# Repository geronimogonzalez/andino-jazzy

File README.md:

<div align="center">

</div>

<div align="center">

</div>

[**UNSTABLE BRANCH**]

Andino is a fully open-source diff drive robot designed for educational purposes and low-cost applications.
It is fully integrated with ROS 2 and it is a great base platform to improve skills over the robotics field.
With its open-source design, anyone can modify and customize the robot to suit their specific needs.

_Note: For videos go to [Media](#selfie-media) section._

## :books: Package Summary

- :rocket: [`andino_bringup`](./andino_bringup): Contains mainly launch files in order to launch all related driver and nodes to be used in the real robot.
- :robot: [`andino_hardware`](./andino_hardware): Contains information about the Andino assembly and hardware parts.
- :ledger: [`andino_description`](./andino_description): Contains the URDF description of the robot.
- :hammer_and_pick: [`andino_firmware`](./andino_firmware): Contains the code be run in the microcontroller for interfacing low level hardware with the SBC.
- :gear: [`andino_base`](./andino_base): [ROS Control hardware interface](https://control.ros.org/master/doc/ros2_control/hardware_interface/doc/writing_new_hardware_interface.html) is implemented.
- :control_knobs: [`andino_control`](./andino_control/): It launches the [`controller_manager`](https://control.ros.org/humble/doc/ros2_control/controller_manager/doc/userdoc.html) along with the [ros2 controllers](https://control.ros.org/master/doc/ros2_controllers/doc/controllers_index.html): [diff_drive_controller](https://control.ros.org/master/doc/ros2_controllers/diff_drive_controller/doc/userdoc.html) and the [joint_state_broadcaster](https://control.ros.org/master/doc/ros2_controllers/joint_state_broadcaster/doc/userdoc.html).
- :world_map: [`andino_slam`](./andino_slam/): Provides support for SLAM with your `andino` robot.
- :compass: [`andino_navigation`](./andino_navigation/): Navigation stack based on `nav2`.

## :paperclips: Related projects

Other projects built upon Andino! :rocket:

- :computer: [`andino_gz`](https://github.com/Ekumen-OS/andino_gz): [Gazebo](https://gazebosim.org/home)(non-classic) simulation of the `andino` robot.
- :lady_beetle: [`andino_webots`](https://github.com/Ekumen-OS/andino_webots): [Webots](https://github.com/cyberbotics/webots) simulation of the Andino robot fully integrated with ROS 2.
- :joystick: [`andino_o3de`](https://github.com/Ekumen-OS/andino_o3de): [O3DE](https://o3de.org/) simulation of the Andino robot.
- :green_circle: [`andino_isaac`](https://github.com/Ekumen-OS/andino_isaac): [Isaac Sim](https://docs.omniverse.nvidia.com/isaacsim/latest/index.html) simulation of the Andino robot.
- :robot: [`andino_rmf`](https://github.com/Ekumen-OS/andino_rmf): [OpenRMF](https://www.open-rmf.org/) integration of Andino simulation.
- :test_tube: [`andino_integration_tests`](https://github.com/Ekumen-OS/andino_integration_tests): Extension to the Andino robot showing how to build integration tests.

## :busts_in_silhouette: Community

 Join our Discord and contribute to the community!

## :pick: Robot Assembly

Visit [`andino_hardware`](./andino_hardware/) for assembly instructions.

## :mechanical_arm: Installation

### Platforms

- ROS 2: Jazzy Jalisco
- OS:
  - Ubuntu 24.04 Noble Numbat
  - Ubuntu Server 24.04.1 (WIP) (On real robot (e.g: Raspberry Pi 4B))

### Build from Source

#### Dependencies

1. Install [ROS 2](https://docs.ros.org/en/jazzy/Installation/Ubuntu-Install-Debs.html)
2. Install [colcon](https://colcon.readthedocs.io/en/released/user/installation.html)

#### colcon workspace

Packages here provided are colcon packages. As such a colcon workspace is expected:

1. Create colcon workspace

```
mkdir -p ~/ws/src
```

2. Clone this repository in the `src` folder

```
cd ~/ws/src
```

```
git clone https://github.com/Ekumen-OS/andino.git
```

3. Install dependencies via `rosdep`

```
cd ~/ws
```

```
rosdep install --from-paths src --ignore-src -i -y
```

4. Build the packages

```
colcon build
```

5. Finally, source the built packages
   If using `bash`:

```
source install/setup.bash
```

`Note`: Whether your are installing the packages in your dev machine or in your robot the procedure is the same.

### Install the binaries

The packages have been also released via ROS package manager system for the 'humble' distro. You can check them [here](https://repo.ros2.org/status_page/ros_humble_default.html?q=andino).

These packages can be installed using `apt` (e.g: `sudo apt install ros-humble-andino-description`) or using `rosdep`.

## :rocket: Usage

### Robot bringup

`andino_bringup` contains launch files that concentrates the process that brings up the robot.

After installing and sourcing the andino's packages simply run.

```
ros2 launch andino_bringup andino_robot.launch.py
```

This launch files initializes the differential drive controller and brings ups the system to interface with ROS.
By default sensors like the camera and the lidar are initialized. This can be disabled via arguments and manage each initialization separately. See `ros2 launch andino_bringup andino_robot.launch.py -s ` for checking out the arguments.

- include_rplidar: `true` as default.
- include_camera: `true` as default.

After the robot is launched, use `ROS 2 CLI` for inspecting environment.
For example, by doing `ros2 topic list` the available topics can be displayed:

    /camera_info
    /cmd_vel
    /image_raw
    /odom
    /robot_description
    /scan
    /tf
    /tf_static

   _Note: Showing just some of them_

### Teleoperation

Launch files for using the keyboard or a joystick for teleoperating the robot are provided.

#### Keyboard

```
ros2 launch andino_bringup teleop_keyboard.launch.py
```
This is similarly to just executing `ros2 run teleop_twist_keyboard teleop_twist_keyboard`.

#### Joystick

Using a joystick for teleoperating is notably better.
You need the joystick configured as explained [here](andino_hardware/README.md#Using-joystick-for-teleoperation).
```
ros2 launch andino_bringup teleop_joystick.launch.py
```

### RViz

Use:

```
ros2 launch andino_bringup rviz.launch.py
```

For starting `rviz2` visualization with a provided configuration.

## :compass: Navigation

The [`andino_navigation`](./andino_navigation/README.md) package provides a navigation stack based on the great [Nav2](https://github.com/ros-planning/navigation2) package.

https://github.com/Ekumen-OS/andino/assets/53065142/29951e74-e604-4a6e-80fc-421c0c6d8fee

Follow the [`andino_navigation`'s README](./andino_navigation/README.md) instructions for bringing up the Navigation stack in the real robot or in the simulation.

## :selfie: Media

### RVIZ Visualization

https://github.com/Ekumen-OS/andino/assets/53065142/c9878894-1785-4b81-b1ce-80e07a27effd

### Slam

Using the robot for mapping.

https://github.com/Ekumen-OS/andino/assets/53065142/283f4afd-0f9a-4d37-b71f-c9d7b2f3e453

https://github.com/Ekumen-OS/andino/assets/53065142/d73f6053-b422-4334-8f62-029a38799e66

See [`andino_slam`](./andino_slam/) for more information.

## :robot: Share your Andino!

Have you built your `Andino` already? Please go to [`Show & Tell`](https://github.com/Ekumen-OS/andino/discussions/categories/show-and-tell) Discussion and share with us your own version of it.

## :star2: Inspirational sources

This section is dedicated to recognizing and expressing gratitude to the open-source repositories that have served as a source of inspiration for this project. We highly recommend exploring these repositories for further inspiration and learning.

 * [articubot_one](https://github.com/joshnewans/articubot_one)
 * [diffbot](https://github.com/ros-mobile-robots/diffbot)
 * [noah_hardware](https://github.com/GonzaCerv/noah-hardware)
 * [linorobot](https://github.com/linorobot/linorobot2)

## :raised_hands: Contributing

Issues or PRs are always welcome! Please refer to [CONTRIBUTING](CONTRIBUTING.md) doc.

## Code development

Note that a [`Docker`](./docker) folder is provided for easy setting up the workspace.

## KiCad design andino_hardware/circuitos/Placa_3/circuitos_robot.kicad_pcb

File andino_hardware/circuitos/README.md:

# Robot Andino
###### Repositorio de la rama de _Geronimo Ferraris_

## Introducción:

En esta rama tomada de la **rama main** del repositorio general agregaré las carpetas y archivos que creo necesario para la construcción del **Robot Andino**.

### Carpeta _circuitos_
Esta carpeta contiene los archivos de kicad donde estará un esquemático de los circuitos necesarios para el robot. A su vez estarán también los archivos necesarios para la creación del **PCB**. 

### Carpeta _imagenes_
Aquí estarán todas las imágenes de los distintos procesos realizados durante la creación del robot.

### Archivo _informe_
Este archivo contiene un registro de lo que se hizo cada día, además de objetivos para el próximo día.

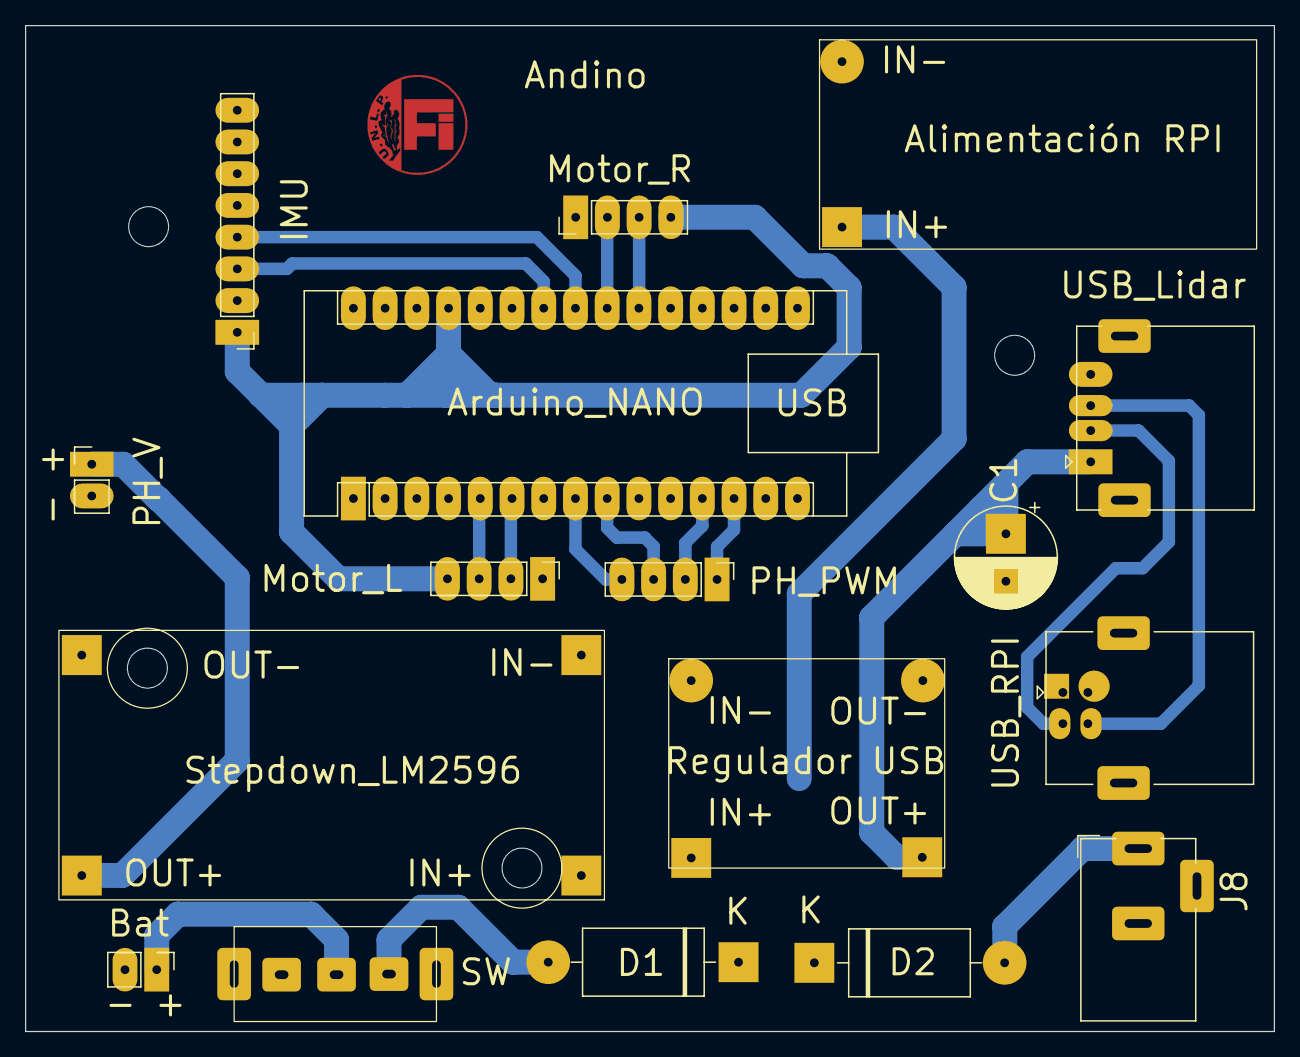
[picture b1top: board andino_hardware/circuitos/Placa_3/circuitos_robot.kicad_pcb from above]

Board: 2 copper layers, 100.0 x 80.5 mm, 17 parts (0 on the bottom side), 20 nets.

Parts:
Alimentación RPI: Regulador_RPI
Arduino_NANO: Arduino_Nano_Every; Arduino_Nano
Bat: PinHeader_1x02_P2.54mm_Vertical
C1: CP_Radial_D8.0mm_P3.80mm
D1, D2: 1N5822; D_DO-201AD_P15.24mm_Horizontal
IMU: Conn_01x08_Pin; PinHeader_1x08_P2.54mm_Vertical
J8: Jack-DC; BarrelJack_CUI_PJ-102AH_Horizontal
Motor_L: Conn_01x04_Pin; PinHeader_1x04_P2.54mm_Vertical
Motor_R: Conn_01x04_Pin; PinHeader_1x04_P2.54mm_Vertical
PH_PWM: Conn_01x04_Pin; PinHeader_1x04_P2.54mm_Vertical
PH_V: PinHeader_1x02_P2.54mm_Vertical
Regulador USB: Regulador_USB
SW: SW_17,2*7,6; SW_17,2_7,6
Stepdown_LM2596: Stepdown_LM2596
USB_Lidar: USB_A; USB_A_CONNFLY_DS1095-WNR0
USB_RPI: USB_B; USB_B_Lumberg_2411_02_Horizontal

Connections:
5V: C1.1, Regulador USB.4, USB_Lidar.1 (VBUS)
5V_Ard: Arduino_NANO.27 (+5V), IMU.1, Motor_L.4, Motor_R.4
9V: PH_V.1, Stepdown_LM2596.3
12V: Alimentación RPI.2, D1.1 (K), D2.1 (K), Regulador USB.2, Stepdown_LM2596.1
12V_Bateria: Bat.1, SW.2
12V_Fuente: D2.2 (A), J8.1
D+: USB_Lidar.3 (D+), USB_RPI.3 (D+)
D-: USB_Lidar.2 (D-), USB_RPI.2 (D-)
Encoder_L_pinA: Arduino_NANO.21 (A2), Motor_R.3
Encoder_L_pinB: Arduino_NANO.22 (A3), Motor_R.2
Encoder_R_pinA: Arduino_NANO.5 (D2), Motor_L.3
Encoder_R_pinB: Arduino_NANO.6 (D3), Motor_L.2
GND: Alimentación RPI.1, Arduino_NANO.4 (GND), Arduino_NANO.29 (GND), Bat.2, C1.2, IMU.2, J8.2, Motor_L.1, Motor_R.1, PH_V.2, Regulador USB.1, Regulador USB.3, SW.4, Stepdown_LM2596.2, Stepdown_LM2596.4, USB_Lidar.4 (GND), USB_Lidar.5 (Shield), USB_RPI.4 (GND), USB_RPI.5 (Shield)
unnamed: D1.2 (A), SW.3
PWM1: Arduino_NANO.8 (D5), PH_PWM.4
PWM2: Arduino_NANO.12 (D9), PH_PWM.2
PWM3: Arduino_NANO.9 (D6), PH_PWM.3
PWM4: Arduino_NANO.13 (D10), PH_PWM.1
SCL: Arduino_NANO.24 (SCL/A5), IMU.3
SDA: Arduino_NANO.23 (SDA/A4), IMU.4

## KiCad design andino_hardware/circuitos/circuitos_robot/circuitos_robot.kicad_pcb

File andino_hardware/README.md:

# andino_hardware

This package aims to provide the necessary information to the correct assembly of the robot.

## Bill of Materials

| Number | Module | Part | Links | Comments |
|:--:|:--:|:-----------------------:|:--------------------:|:-------------------------------------------------------:|
| 1 | SBC | Raspberry Pi 4 B (4 Gb) | [PiShop](https://www.pishop.us/product/raspberry-pi-4-model-b-2gb/), [TiendaTec](https://www.tiendatec.es/raspberry-pi/gama-raspberry-pi/1100-raspberry-pi-4-modelo-b-4gb-5056561800349.html) | If you want better performance you could buy the 8GB model |
| 2 | Chassis |  2 x Print 3d Chassis + Rubber Tyre Wheels | [Chassis](./printing_model/chassis/), [Wheels Sparkfun](https://www.sparkfun.com/products/13259) | - |
| 3 | Motors | 2 x Motor with Encoder | [Sparkfun](https://www.sparkfun.com/products/16413) | - |
| 4 | Microcontroller | Arduino Nano | [Amazon](https://www.amazon.es/RUIZHI-Interfaz-Controlador-Mejorada-Compatible/dp/B0CNGKG4MZ/ref=sr_1_6?dib=eyJ2IjoiMSJ9.gnHfW9VtlEjMns12dAyHXLyFAlaikWpFyoOQJpO0iJBR-zelggQTQ9n001SH_P6NQ9DO3gPetP2krm7GAGvJus6vz4Utqu8Hy1gol0Rq7nmtJITd70ZNi3linf9v1g1iP7MlBx98cBGLVvFy-O2kZnJ63uZDwOZzwz_kExJzUWAxroO3AjufqqGOQHswLfDfjH6jpOJt54xxpCaqurDccId2O0uGKOj6WpPz6iLSubpsPB479SWYPSncxWQzz2kO4VjT6HVzPS2uWi19TS-A9WXVZceLBiz9t25Pf39jiGQ.1sLxrQ94HdIoXBq4VcDFMZhzKoL3wyJoY-U6BmDI6fY&dib_tag=se&keywords=arduino+nano+v3&qid=1714468231&sr=8-6) | You can also use an Arduino Uno, but mind size. It should include a microUSB - USB cable. If not, you will need to purchase it.  |
| 5 | Motor Driver | L298N Dual H Bridge | [Amazon](https://www.amazon.com/Bridge-Stepper-Driver-Module-Controller/dp/B09T6K9RFZ/ref=sr_1_4?crid=37YY7JO6C3WVE&keywords=l298&qid=1685740618&sprefix=l29%2Caps%2C277&sr=8-4) | - |
| 6 | Laser Scanner | RPLidar A1M8 | [RobotShop](https://www.robotshop.com/products/rplidar-a1m8-360-degree-laser-scanner-development-kit?_pos=3&_sid=b0aefcea1&_ss=r), [Amazon](https://www.amazon.es/dp/B07VLFGT27?ref_=cm_sw_r_cso_wa_apan_dp_RJ3AZC2XCEVDK0X2DCGA&starsLeft=1&th=1) | If no microUSB-USB cable is included, you will need to purchase one |
| 7 | Camera | Raspi Camera Module V2, 8 MP | [Robotshop](https://www.robotshop.com/products/raspberry-pi-camera-module-v2), [Amazon](https://www.amazon.com/Raspberry-Pi-Camera-Module-Megapixel/dp/B01ER2SKFS?th=1), [Longer cable](https://www.amazon.es/AZDelivery-Repuesto-Raspberry-30cm-Flexkabel/dp/B01NAXKTDP/ref=sr_1_9?__mk_es_ES=%C3%85M%C3%85%C5%BD%C3%95%C3%91&crid=I1IK0FQVQCCU&dib=eyJ2IjoiMSJ9.2UYb-3a8M00iHZZiHT0xjp8vfzq-3BSmJSLxdtcCMV6WMj8g5T8T_j5DKX8cESxqnVN01YpV3nX28IuhewGTOsmJ4yF5st20TxU7kHNHftZE_aygB5vT-001wEvUfx70V0H0DZljw0YfC4R2wpjsTR_89pAA95C4F8LhJiGbbUGTEjBgmjnsRIFs6FYatZa9KVusNyv2cKxGZlav36gdoAkMXQUvX578c6frxSnH5DROCeK6bKSqrczA7R8OBVWC995fK1AxHbJLHZJEDQGXMVhUkHd2liBV0nq48mnyE6Q.nHty4TxSpldkH8FZAia_rx7sX6c2uIBpPRUEqwq5NiY&dib_tag=se&keywords=raspberry%2Bpi%2Bcamera%2Bcable&qid=1716878948&sprefix=raspberry%2Bpi%2Bcamera%2Bcable%2Caps%2C76&sr=8-9&th=1)  | A link for a longer cable (30 cm) is included, just in case the one included with the camera is too short. |
| 8 | Electrical Power Supply | Powerbank 5V | [Amazon](https://www.amazon.es/Heganus-Powerbank-10000mAh-port%C3%A1til-pr%C3%A1ctico/dp/B082PPPWXY/ref=asc_df_B082PPPWXY/?tag=googshopes-21&linkCode=df0&hvadid=420334509253&hvpos=&hvnetw=g&hvrand=13392500367381615369&hvpone=&hvptwo=&hvqmt=&hvdev=c&hvdvcmdl=&hvlocint=&hvlocphy=9181150&hvtargid=pla-878722533582&psc=1&mcid=642b7553488f350a8726c7bfb183a667&tag=&ref=&adgrpid=95757266066&hvpone=&hvptwo=&hvadid=420334509253&hvpos=&hvnetw=g&hvrand=13392500367381615369&hvqmt=&hvdev=c&hvdvcmdl=&hvlocint=&hvlocphy=9181150&hvtargid=pla-878722533582) | Any powerbank is suitable: Mind size / weight / output current(>=2A) |
| 9 | Power Step up | DC - DC boost converter | [Amazon Europe](https://www.amazon.es/Convertidor-convertidor-Controlador-almacenamiento-Transformadores/dp/B08D5XF571) | If motors support higher voltage than 5V a step-up(e.g: to 9V) can be added between powerbank (5V) and motor driver. Screw clockwise to reduce the output voltage. |
| 10 | Fixing & Mount | M3 bolts/fasteners - M3 Spacers - M2.5/2.0 bolts/fasteners for SBC | [Mercado Libre](https://articulo.mercadolibre.com.ar/MLA-823234605-kit-tornillos-electronica-500-unid-fresada-philips-m3-oferta-_JM#position=1&search_layout=stack&type=item&tracking_id=2a14497e-a3dc-4a0f-98fb-b3b524117284), [Amazon](https://www.amazon.com/Taiss-620PCS-Metric-Assortment-Washers/dp/B0CWXRG6VL/ref=sr_1_2_sspa?crid=3R3BT7LOQWZ4B&dib=eyJ2IjoiMSJ9.EBY3VtTnCGRri20ECsEwpF2eTrWOhlADXq8Rbv78LP7JVW0giUfPQ5-G3e5cVq7svNoKIPbFGf0jQoImIPuJvU72yWC0XaaXyHE03TjX1zVT-AxcCUr6bvvqnQrrwFNowZjHy2ZibnHX4sDMx3aixEmx5XUGq43KVEID5FIGzTw6xsLQd410DewktxUFWCHLSD8HR8BeAUKcP3mzciuPmc8dcz9TzY5cZ_wYFO-WyEQ.B5-OkrGZbzkIn8cw4Zb_LtQUoxX1qKuiVqI6PTNmpZk&dib_tag=se&keywords=kit+M3+tuercas+y+tornillos&qid=1714469030&sprefix=kit+m3+tuercas+y+tornillos%2Caps%2C149&sr=8-2-spons&sp_csd=d2lkZ2V0TmFtZT1zcF9hdGY&psc=1), [Spacers](https://www.amazon.es/YOKIVE-Separadores-Tornillos-Hexagonal-Consistente/dp/B0BWXL75R6/ref=sr_1_11?__mk_es_ES=%C3%85M%C3%85%C5%BD%C3%95%C3%91&crid=39R5HOTYH2AC9&dib=eyJ2IjoiMSJ9.7A-mx6__B2agU-KSbpRPhlNj2WkQfkj8OtZKEmwlwHa3NiDqUA-1Um0339r3Ssad0h03L471s08VcgBGByJpKwummUR8Sgyt3AuF4sahKIacNlyBlD8mcl3bNQ54HR8L585aepoUOxllFXUi2AEGde8kjkNqaiOEcyflppOf1eKtAtlyTYnnjOVJs5YqRK97QV3pUt1g8Rt1zLn7RsEtRrvlMQIXXBjIFFZsqK2tN7OBY2lgorgdRsXP1aS5tad9rD9vsl9SkPUx_c1Bf0ulzabNSFk19v_cSd0IwEx2zSw.30hsx31Q_-5A3eLrlOwhoTvAs_yDufCk04NiN0xk0C8&dib_tag=se&keywords=spacer+30mm+m3&qid=1716156793&refinements=p_n_free_shipping_eligible%3A20930980031&rnid=20930979031&sprefix=spacer+30mm+m3%2Caps%2C107&sr=8-11) | You will probably need to replace the default spacers for the LiDAR with M3 spacers |
| 11 | Other 3D printed parts | Camera Mount | [3D models](./printing_model/raspi_cam_mount/) | These parts are for fixing the Raspi Cam at the front of the robot |
| 12 | Caster wheel | Caster wheel | [Amazon](https://www.amazon.es/Unidades-Peque%C3%B1as-Dispositivo-Transferencia-Transporte/dp/B098XHYW7F/ref=asc_df_B098XHYW7F/?tag=googshopes-21&linkCode=df0&hvadid=529604577974&hvpos=&hvnetw=g&hvrand=15132275207682237467&hvpone=&hvptwo=&hvqmt=&hvdev=c&hvdvcmdl=&hvlocint=&hvlocphy=9181150&hvtargid=pla-1396749454795&psc=1&mcid=b1df85a65d163e89b507de60e73f9e65) | - |
| 13 | SD Card | 64 GB SD Card | [Apokin](https://www.apokin.es/tarjeta-microsd-philips-64gb-class10.html), [Amazon](https://www.amazon.es/Kingston-Tarjeta-SDCS2-64GB-Adaptador/dp/B07YGZQ4H8/ref=sr_1_7?dib=eyJ2IjoiMSJ9.zE4PI6DCNK3d78rtl5ga1NQXGwJT1jC2iqi3mXNzbdJ4BosAUPCn9gc13Gc7pdHDx-7wTy4CDj0zIlgDpu9qXH-6GLgI--pJbfi3OvTBPhwwH-tfi1OzM9xqcAOJG6pJuTtkknsyFk6Ma2EHJ4UdheaziDC_KKaWNKgsf_DFbcA-ZxQSXlTtQqwHvCzgi8hq4vKGiEIY-LSZS_sXE9IUGroo0Isl59Po2IXhTBG5IHnnsVR_7lo0dVBVFYl-5GY2CvJbrixULuPl90TbFTTP6DoIeDcpFdDTcbvSK3Lecss.WXBgIZllFgQxx13Szl3q6WIlTOliwrN8V42J1SzNJ8o&dib_tag=se&qid=1714552555&refinements=p_n_feature_browse-bin%3A948155031&s=computers&sr=1-7) | The SD Card is used to host the OS for the Raspberry Pi |
| 14 | (Optional) Plastic seals | - | - | You will need at least 2 longer ones to fix the powerbank to the upper chassis, and the shorter ones for all the wires. If you don't want to use them, you can use other method to fix the powerbank and wires |

When you gather all the parts, you should have the following (NOTE: the printed encoder wheels are no longer necessary, since the motors are equipped with an embedded encoder):

### Tooling

| Number | Tool | Links | Comments |
|:--:|:------:|:--------------------:|:-------------------------------------------------------:|
| 1 | Set of screwdrivers | [Amazon](https://www.amazon.es/Ainiv-Destornilladores-Precisi%C3%B3n-Destornillador-magnetizador/dp/B09CD1F44B/ref=asc_df_B09CD1XT57/?tag=googshopes-21&linkCode=df0&hvadid=529495276761&hvpos=&hvnetw=g&hvrand=2854754490438163902&hvpone=&hvptwo=&hvqmt=&hvdev=c&hvdvcmdl=&hvlocint=&hvlocphy=9181160&hvtargid=pla-1431590275356&mcid=4f49c0c6c8ca33b390169090ae4ad15b&th=1) | You need flat and star screwdrivers |
| 2 | Silicon Pistol | [Amazon](https://www.amazon.es/Tilswall-Pegamento-Manualidades-Bricolaje-Reparaciones/dp/B07TD1RD4R/ref=pd_ci_mcx_pspc_dp_d_2_i_1?pd_rd_w=49k0d&content-id=amzn1.sym.f11fe75a-7397-412e-9b90-7e09bf6f5c14&pf_rd_p=f11fe75a-7397-412e-9b90-7e09bf6f5c14&pf_rd_r=MA73TQJTYS2GMC7XW7YC&pd_rd_wg=Z3aRz&pd_rd_r=08e805c6-81b7-4023-8ea1-9b357536cba1&pd_rd_i=B07TD1RD4R&th=1) | This pistol should include 75 silicon bars so you won't need to purchase them separately |

## Assembly Process

  1. Screw the Motor Driver and the idler wheel to the lower chassis.

  Here you have a front image of how the caster wheel are mounted to the chassis:

  2. Screw the 3D printed parts for the Raspi Camera Module:

  3. Add the Arduino Nano to the back of the lower part of the chassis. It should look like this:

  4. Screw the Raspberry Pi and the DC-DC converter to the front of the lower part of the chassis:

  5. Fix the powerbank to the back of the upper part of the chassis:

  6. Add the RPLidar to the front of the upper part of the chassis:

  7. Add the IMU (WIP)

  <!-- TODO Add photo of the IMU physical implementation-->

  8. Perform all the wiring following the [Connections Diagram](#connection-diagram) of both the upper and lower chassis. Note that some of the connections may need to be done by soldering the cables.

  9.  Join both chassis together, and complete the remaining wiring to have your robot ready:

## Connection Diagram

### Motor-Arduino

Some frequent errors:
 - If one of the motors rotates in the opposite direction (think about the orientation of the motors in the chassis) probably the output(+ and -) of the L298N's output should be toggled.
 - When moving forward the encoder values should increase while moving backwards they should decrease. If it is happening the other way around probably the A and B encoder signals should be toggled.

### Raspberry-Power

*NOTE: depending on the power bank maximum output current, the motors may need to be powered with a voltage value lower than 9V. While a higher voltage value (up to 9V) leads to smoother operation (better motor speed control), it also increases their open-loop speed, which is noticeable particularly during motion start and varies according to the power bank quality (output current capabilities). Therefore, adjusting the output voltage to lower values (around 7V) may be required so as to make the motors work as expected.

**NOTE: Ensure the ribbon cable is properly connected with the blue or silver side facing the USB ports.

## Microcontroller Configuration

For uploading the microcontroller firmware please refer to [`andino_firmware`](../andino_firmware/README.md) package.

## Single Board Computer (SBC)

The SBC used in this project is a Raspberry Pi 4b so the guidelines here will refer particularly to this family of on-board computers, however extending its use to other families is possible as well.

### Operative System [WIP]

Ubuntu Server 24.04.1 is the recommended operative system for this project if you want to use the `jazzy` distro, since Ubuntu Mate 24 is not yet released.

For installing this OS in the Raspberry:
1. Download the image from here: [download Ubuntu 24 for Raspberry](https://ubuntu.com/download/raspberry-pi)

2. Install OS to a microSD card using [Raspberry Pi Imager](https://www.raspberrypi.com/software/).
   - No extra configuration should be necessary.

3. Boot your raspberry using the microSD and a HDMI connection. Some initial configuration is necessary. Follow the wizard for a proper set up. It is recommended to use simple User and Password combinations for the user. For example:
    - user: pi
    - password: admin
      
**recordar que el primer arranque debe ser conectado a internet mediante cable ethernet**

4. Once is done, run `sudo apt update && sudo apt upgrade` in a terminal for updating the system. Then reboot.

Para configurar la conecxion wifi descargar el paquete network manager
```
sudo apt-get install network-manager
```
y utilizar el comando 
```
sudo nmtui
```
para la configuracion de la red wifi deseada.

Recomendacion: Siempre trabajar con la mayor velocidad posible, por lo que si es posible trabajar bajo wifi 5.0 o cableado al menos una de las computadoras (ROV o station).
### Installing dependencies

Some packages are necessary to be installed towards a correct set up of the robot's on-board computer.

#### ssh-server

In general, you will want to access to the Raspberry remotely via `ssh` connection while being connected in the same network.
So we need to install `ssh-server`;
```
sudo apt-get install openssh-server
```
Enable it if it is not enabled yet:
```
sudo systemctl enable ssh --now
```

After this you will be able to access this device from a remote computer by doing:
```
ssh <user>@<ip>
```
For example if the user is `pi` and the ip is `192.168.0.102`
```
ssh pi@192.168.0.102
```

#### Common utilities

Install some common utilities that will be required later on.

```
sudo apt update
```

```
sudo apt install git net-tools software-properties-common build-essential -y
```
<font color="red"> el comando de abajo no existe. No lo corro y veo</font>

```
sudo apt install python3-rosdep2 python3-catkin-pkg python3-catkin-pkg-modules python3-rospkg-modules python3-rospkg  -y
```

#### Install ROS

Follow suit the instructions for installing next dependencies from binaries:
 - [ROS 2 Jazzy](https://docs.ros.org/en/jazzy/Installation/Ubuntu-Install-Debs.html)

Nota: Instalar ROS Jazzy Desktop, ya que contiene instaladas herramientas necesarias.

To automatically source ROS installation, it is recommended to add `source /opt/ros/humble/setup.bash` line to the `~/.bashrc` file.

#### Arduino

Arduino drivers are necessary for the SBC (Raspberry) <--> Microcontroller(Arduino) serial communication.

```
sudo apt install arduino
```

Configure it properly:
1. Add user to `dialout` and `plugdev` groups:
   ```
   sudo usermod -a -G dialout $USER
   ```
   ```
   sudo usermod -a -G plugdev $USER
   ```
   Note you will need a reboot after this to be effective.

#### Raspberry Camera Module V2

After connecting the camera module to the Raspberry's camera port.
```
sudo apt install libraspberrypi-bin v4l-utils
```
```
sudo usermod -aG video $USER
```

Check camera status:
```
vcgencmd get_camera
```

If the output of the previous command is `supported=1 detected=1', everything is fine. If not, your camera won't work correctly, you need to perform some configuration first.

Modify the `config.txt` file for the boot:

```sh
 sudo nano /boot/firmware/config.txt
```

And add these lines:

```
# Autoload overlays for any recognized cameras or displays that are attached
# to the CSI/DSI ports. Please note this is for libcamera support, *not* for
# the legacy camera stack
start_x=1
gpu_mem=128
```

Save and close the file. Then we need to enable the camera support for the raspberry:

```sh
sudo raspi-config
```

Go to `Interface Options`, select `camera` and enable it.

Finally, you just need to reboot and the camera should be working fine.

#### RPLidar installation

The installation of the A1M8 RPLidar sensor is quite straight forward and a ros integration package will be installed later on via `rosdep`.

For now, after connecting it to the usb port:
 1. Verify USB connection: Green light in the usb conversor(A1M8 side board) should be turned on.
 2. Check the authority of RPLidar's serial-port:
    - `ls -l /dev |grep ttyUSB`
    - Add extra bits by doing `sudo chmod 666 /dev/ttyUSB<number_of_device>`

### USB Port name configuration

#### Fixed USB port names

As having multiple USB devices connected to the USB ports of the Raspberry Pi, the automatically assigned USB port numbers could unexpectedly change after a reboot.
To avoid assigning your device to a `tty_USBX` number that isn't the correct one we should assign fixed USB port name for each connected device.

The idea is to be able to generate a link between the real `ttyUSBX` port and an invented one. For this we will need to create rules, that every time the Raspberry Pi boots are executed, and therefore we
always point to the correct port name.

In order to create fixed names for the USB devices follow the instructions:

1. Check the devices you have connected:
    ```
    sudo dmesg | grep ttyUSB
    ```

    ```
    [  10.016170] usb 1-1.2: ch341-uart converter now attached to ttyUSB0
    [ 309.186487] usb 1-1.1: cp210x converter now attached to ttyUSB1
    ```
    In the setup where this was tested we have:
      -> Arduino Microcontroller -> _usb 1-1.2: ch341-uart converter now attached to ttyUSB0_
      -> A1M8 Lidar Scanner -> _usb 1-1.1: cp210x converter now attached to ttyUSB1_

    _Note: If you don't know how to identify each one you can simply connect them one by one and check this output._

2. Look for attributes for each device that we will use to anchor a particular device with a name.
  We will use the `idProduct` and `idVendor` of each device.
   - Arduino Microcontroller:
      ```
      udevadm info --name=/dev/ttyUSB0 --attribute-walk
      ```
      You should look for the `idProduct` and `idVendor` under the category that matches the usb number(1-1.X):
      In this case the `ttyUSB0` was referenced to the `usb 1-1.2`, so go to that section and find the ids:
      ```
        ATTRS{idProduct}=="7523"
        ATTRS{idVendor}=="1a86"
      ```
   - Lidar Scanner
      ```
      udevadm info --name=/dev/ttyUSB1 --attribute-walk
      ```
      In this case the `ttyUSB0` was referenced to the `usb 1-1.1`, so go to that section and find the ids:
      ```
        ATTRS{idProduct}=="ea60"
        ATTRS{idVendor}=="10c4"
      ```

3. Create the rules:

    Open the file:
    ```
    sudo nano /etc/udev/rules.d/10-usb-serial.rules
    ```

    Add the following:

    ```
    SUBSYSTEM=="tty", ATTRS{idProduct}=="7523", ATTRS{idVendor}=="1a86", SYMLINK+="ttyUSB_ARDUINO"
    SUBSYSTEM=="tty", ATTRS{idProduct}=="ea60", ATTRS{idVendor}=="10c4", SYMLINK+="ttyUSB_LIDAR"
    ```
    Note that in the `symlink` field a fixed name is indicated.

4. Re-trigger the device manager:
    ```
    sudo udevadm trigger
    ```

5. Verify
    ```
    ls -l /dev/ttyUSB*
    ```
    ```
    crw-rw---- 1 root dialout 188, 0 Sep  2 15:09 /dev/ttyUSB0
    crw-rw---- 1 root dialout 188, 1 Sep  2 15:09 /dev/ttyUSB1
    lrwxrwxrwx 1 root root         7 Sep  2 15:09 /dev/ttyUSB_ARDUINO -> ttyUSB0
    lrwxrwxrwx 1 root root         7 Sep  2 15:09 /dev/ttyUSB_LIDAR -> ttyUSB1
    ```

Done! You can always use your devices by the fixed names without using the port number.
Here, `ttyUSB_ARDUINO` and `ttyUSB_LIDAR` are fixed names for the Arduino Microcontroller and the Lidar Scanner respectively.

For more information you can take a look at this external tutorial: [Here](https://www.freva.com/assign-fixed-usb-port-names-to-your-raspberry-pi/)

### Create robot workspace

Let's create our workspace and build from source this repository.

```
cd ~
```
```
mkdir robot_ws/src -p
```
Clone this repository in the `src` folder
```
cd robot_ws/src
```
```
git clone <repository_address>
```
Install dependencies via rosdep:
```
cd ~/robot_ws
```
When it is the first time you run `rosdep`:
```
rosdep update
```
Make sure to export the `ROS_DISTRO` environment variable:
```
export ROS_DISTRO=jazzy
```
And then proceed to install the workspace dependencies:
```
sudo apt update
rosdep update
rosdep install --from-paths src --ignore-src -y
```
```
source /opt/ros/jazzy/setup.bash
```
para hacer el source permanente
```
echo "source /opt/ros/jazzy/setup.bash" >> ~/.bashrc
source ~/.bashrc
```
Note that option `-r` has been added. For ARM based processors, there are missing packages, e.g. those related to simulation. We would not try to run the simulation in the compute platform of andino, however for convenience it is added here.

Let' source the ROS Humble installation:
```
source /opt/ros/humble/setup.bash
```
Let's build the packages:
```
colcon build
```
After building is completed:
```
source install/setup.bash
```

After this, you are good to go and use the robot!
Refer to [`usage`](../README.md#usage) section.

### Extra Recommendations & Tools

#### Network
Via terminal the wifi connection can be switched by doing:

List available wifi networks:
```
sudo nmcli dev wifi list
```
Connect to the desired one:
```
sudo nmcli --ask dev wifi connect <SSID>
```

#### Copy files remotely

Using `scp` is a useful tool when copying files remotely over `ssh`.

For copying a folder from host to remote unit:
```
scp -r <path/to/folder> <remote_user>@<remote_ip>:<remote_path_to_folder>
```

#### ROS Domain ID

The domain ID is used by DDS to compute the UDP ports that will be used for discovery and communication.

When using a "public" network using the domain id is a good technique to avoid extra noise with other ROS 2 system in the same network.

See [ROS_DOMAIN_ID](https://docs.ros.org/en/humble/Concepts/Intermediate/About-Domain-ID.html)

TLDR? Export an environment variable with the same ID in **all** ROS 2 clients in the network for a correct discovery.
```
export ROS_DOMAIN_ID=<a_number_between_0_and_101>
```

#### Using joystick for teleoperation

[`andino_bringup`](../andino_bringup/launch/teleop_joystick.launch.py) package provides a launch file for launching the corresponding `ROS 2` nodes for teleoperating the robot using a joystick.

It is worth mentioning that a set up might be needed depending on the gamepad you are using. Here some general guidelines:
 - In case you are using a _Xbox One Controller_ and you want use it wireless (via USB Wirless Dongle) installing [Xone](https://github.com/medusalix/xone) is recommended.
 - Verify that your joystick is actually working on Ubuntu:
    - Some tools that might be useful:
      - `sudo apt install joystick jstest-gtk evtest`
    - Run `evtest` to check if your pad is connected:
      ```
      $ evtest
        No device specified, trying to scan all of /dev/input/event*
        Not running as root, no devices may be available.
        Available devices:
          /dev/input/event22:	Microsoft X-Box One pad

      ```
    - Alternatively, you can use `jstest-gtk` to check the controller, you will find a pretty GUI to play with.

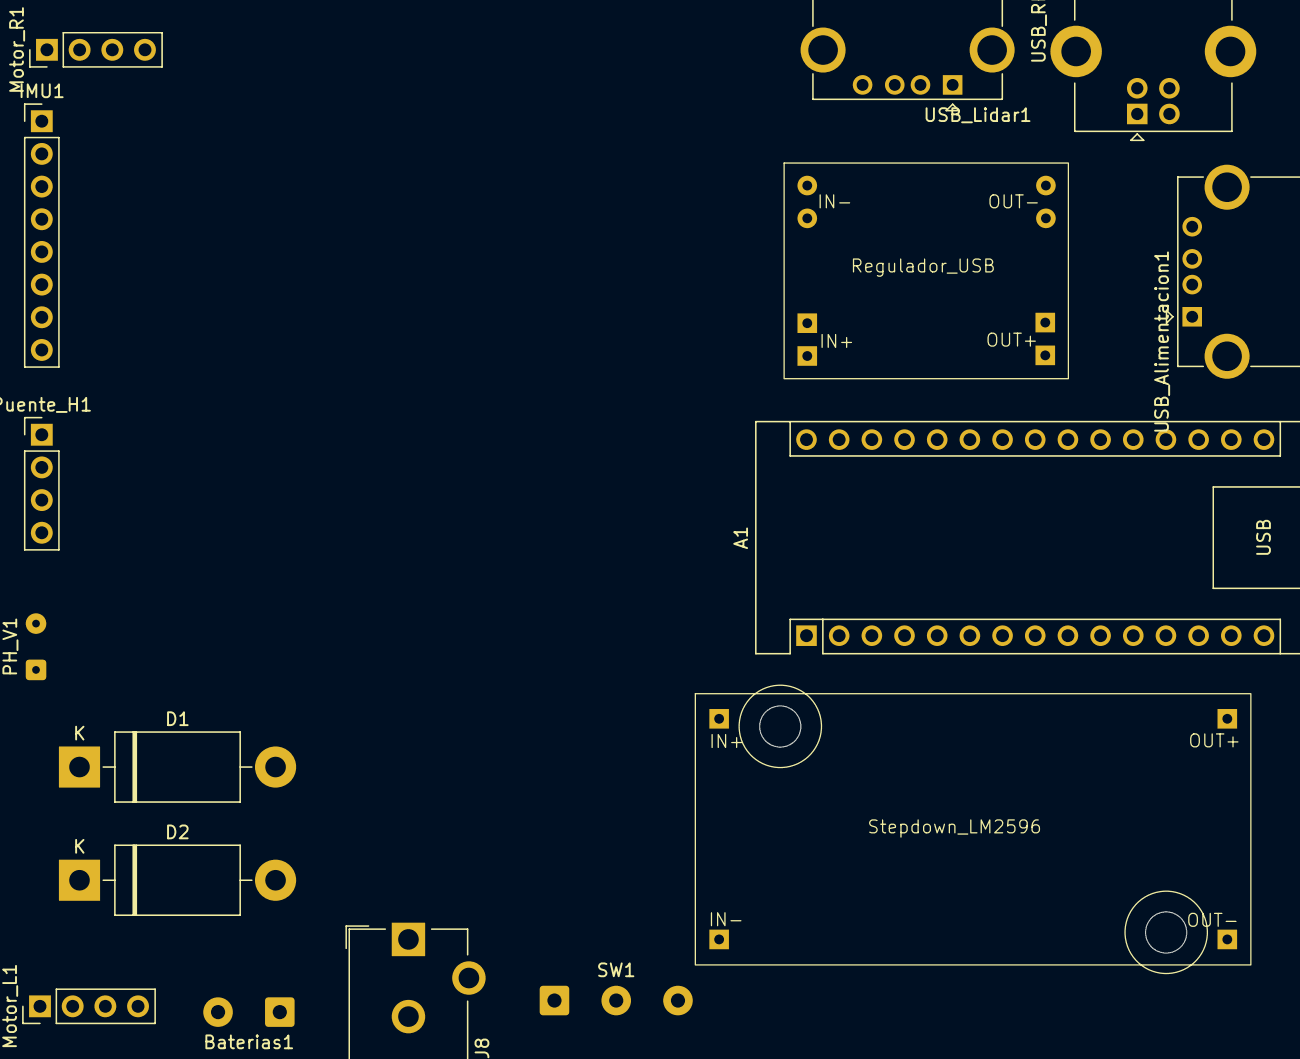
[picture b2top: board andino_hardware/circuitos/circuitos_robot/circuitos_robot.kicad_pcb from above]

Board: 2 copper layers, 16 parts (0 on the bottom side), 22 nets, no tracks yet.

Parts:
A1: Arduino_Nano_Every; Arduino_Nano
Baterias1: Conn_01x02_Pin; SolderWire-0.5sqmm_1x02_P4.8mm_D0.9mm_OD2.3mm
D1, D2: 1N5822; D_DO-201AD_P15.24mm_Horizontal
IMU1: Conn_01x08_Pin; PinHeader_1x08_P2.54mm_Vertical
J8: Jack-DC; BarrelJack_CUI_PJ-102AH_Horizontal
Motor_L1: Conn_01x04_Pin; PinHeader_1x04_P2.54mm_Vertical
Motor_R1: Conn_01x04_Pin; PinHeader_1x04_P2.54mm_Vertical
PH_V1: Conn_01x02_Pin; SolderWire-0.1sqmm_1x02_P3.6mm_D0.4mm_OD1mm
Puente_H1: Conn_01x04_Pin; PinHeader_1x04_P2.54mm_Vertical
Regulador_USB: Regulador_USB
SW1: Conn_01x03_Pin; SolderWire-0.5sqmm_1x03_P4.8mm_D0.9mm_OD2.3mm
Stepdown_LM2596: Stepdown_LM2596
USB_Alimentacion1: USB_A; USB_A_CONNFLY_DS1095-WNR0
USB_Lidar1: USB_A; USB_A_CONNFLY_DS1095-WNR0
USB_RPI1: USB_B; USB_B_Lumberg_2411_02_Horizontal

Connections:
5V: Regulador_USB.7, USB_Alimentacion1.1 (VBUS), USB_Lidar1.1 (VBUS)
5V_Ard: A1.27 (+5V), IMU1.1, Motor_L1.4, Motor_R1.4
9V: A1.30 (VIN), PH_V1.2, Stepdown_LM2596.3
12V: D1.1 (K), D2.1 (K), Regulador_USB.3, Stepdown_LM2596.1
12V_Bateria: Baterias1.1, SW1.2
12V_Fuente: D2.2 (A), J8.2
Encoder_L_pinA: A1.21 (A2), Motor_L1.3
Encoder_L_pinB: A1.22 (A3), Motor_L1.2
Encoder_R_pinA: A1.5 (D2), Motor_R1.3
Encoder_R_pinB: A1.6 (D3), Motor_R1.2
Flash: IMU1.7, Regulador_USB.2
GND: Baterias1.2, IMU1.2, J8.1, Motor_L1.1, Motor_R1.1, PH_V1.1, Regulador_USB.6, Stepdown_LM2596.2, Stepdown_LM2596.4, USB_Alimentacion1.4 (GND), USB_Lidar1.4 (GND), USB_RPI1.4 (GND)
unnamed: A1.4 (GND), A1.29 (GND)
unnamed: D1.2 (A), SW1.3
unnamed: USB_Lidar1.3 (D+), USB_RPI1.3 (D+)
unnamed: USB_Lidar1.2 (D-), USB_RPI1.2 (D-)
PWM1: A1.8 (D5), Puente_H1.4
PWM2: A1.12 (D9), Puente_H1.3
PWM3: A1.9 (D6), Puente_H1.2
PWM4: A1.13 (D10), Puente_H1.1
SCL: A1.24 (SCL/A5), IMU1.3
SDA: A1.23 (SDA/A4), IMU1.4

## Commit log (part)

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2025-10-09 Primer commit
2025-10-22 estoy probando
2025-10-22 creacion de carpetas necesarias
2025-10-23 agregue carpeta para las imagenes del proceso de construccion
2025-10-24 añadi primer README
2025-10-25 Clean up README formatting and content
    Removed unnecessary HTML tags and logos from README.
2025-10-25 Update connection details in README.md
    Updated README to reference 'hw.h' for connection details.
2025-10-30 Progreso_30/10/25
2025-11-02 update SLAM node funtional
2025-11-05 progreso_5/11_Componentes
2025-11-05 Progreso_30/10/25_2(planteo_placa)
2025-11-09 Enhance README with setup and Wi-Fi instructions
    Added instructions for initial setup and Wi-Fi configuration.
2025-11-09 Update README with Ethernet connection note for boot
    Added a note about the initial boot requiring an Ethernet connection for internet access.
2025-11-14 Update README with installation instructions and notes
    Corrected a note about the first boot and updated installation commands.
2025-11-15 Add ROS 2 Jazzy installation instructions
    Updated installation instructions to include ROS 2 Jazzy and added a note about installing Jazzy Desktop.
2025-11-18 Agregar navigation2 como carpeta normal
2025-11-18 Change ROS_DISTRO to 'jazzy' and update commands
    Updated ROS distribution from 'humble' to 'jazzy' and modified installation commands.
2025-12-04 cambios 4_12_25
2026-04-24 Primera placa impresa
2026-05-14 instalacion rpi
2026-05-28 carga datos 28/5
2026-05-28 arreglo versiones pcs
2026-06-11 actualizacion 11-6-26
2026-06-11 placa
